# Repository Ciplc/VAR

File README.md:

# VAR
The VAR repository.
For those of you new to C++ here are two resources that I found helpful:
http://www.learncpp.com/
https://www.youtube.com/watch?v=mUQZ1qmKlLY

For those of you new to Python, talk to me for help in addition to
looking up several tutorials online, most tutorials are perfectly 
fine to learn from. Learning by doing is a great technique.

To commit to master you must verify your commits using GPG keys. Merging requires 1 reviewer.

## Acronyms

**ERPI** : Emulated Rasperry Pi

**RPI**  : Rasperry Pi

**RTC**  : Real time clock

**CMP**  : Civilian Missiles Program

**PS**   : Project Stratosphere

**-v**   : Version

**ASS**  : Acronyms Seriously Suck

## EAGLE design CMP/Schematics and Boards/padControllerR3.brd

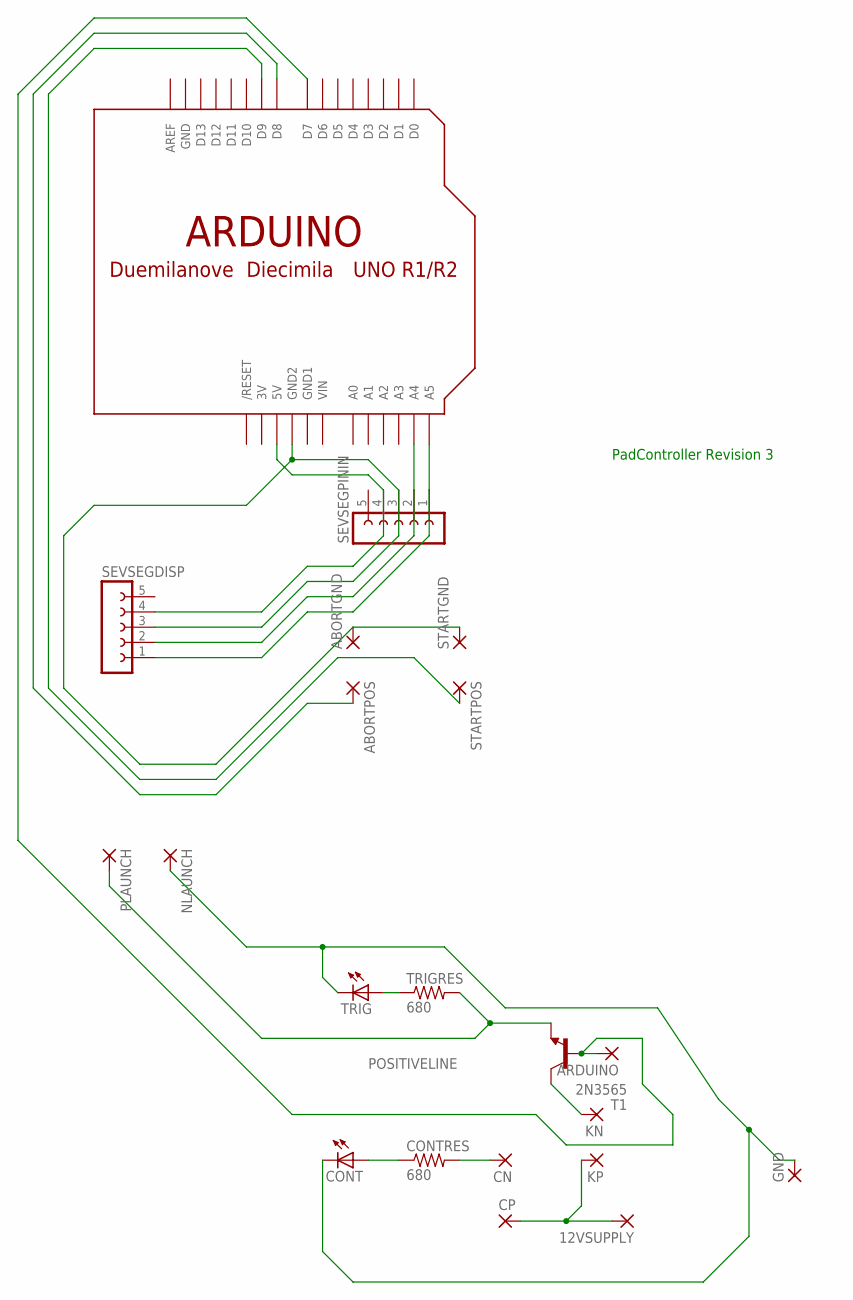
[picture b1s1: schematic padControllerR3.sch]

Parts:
12VSUPPLY: 3,17/1,1
ABORTGND: 3,17/1,3
ABORTPOS: 3,17/1,3
ARDUINO: 3,17/1,3
CN: 3,17/1,3
CONT: LED3MM
CONTRES: 680; 0207/7
CP: 3,17/1,3
GND: 3,17/1,1
KN: 3,17/1,3
KP: 3,17/1,3
NLAUNCH: 3,17/1,1
PLAUNCH: 3,17/1,1
SEVSEGDISP: FE05-1
SEVSEGPININ: FE05-1
STARTGND: 3,17/1,3
STARTPOS: 3,17/1,3
T1: 2N3565; TO92
TRIG: LED3MM
TRIGRES: 680; 0207/7
U$1: ARDUINO-NOHOLE

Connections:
3V: U$1.3V
GND: U$1.GND
GND1: U$1.GND1
unnamed: 12VSUPPLY.1, CP.1, KP.1
unnamed: KN.1, T1.1 (C)
unnamed: ABORTPOS.1, U$1.D8
unnamed: SEVSEGDISP.4, SEVSEGPININ.4, U$1.5V
unnamed: TRIG.A, TRIGRES.1
unnamed: CONT.K (C), GND.1, NLAUNCH.1, TRIG.K (C)
unnamed: CN.1, CONTRES.2
unnamed: CONT.A, CONTRES.1
unnamed: ARDUINO.1, T1.2 (B), U$1.D7
unnamed: STARTPOS.1, U$1.D9
unnamed: ABORTGND.1, SEVSEGDISP.3, SEVSEGPININ.3, STARTGND.1, U$1.GND2
unnamed: SEVSEGDISP.2, SEVSEGPININ.2, U$1.A4
unnamed: SEVSEGDISP.1, SEVSEGPININ.1, U$1.A5
POSITIVELINE: PLAUNCH.1, T1.3 (E), TRIGRES.2
VIN: U$1.VIN

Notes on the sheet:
PadController Revision 3

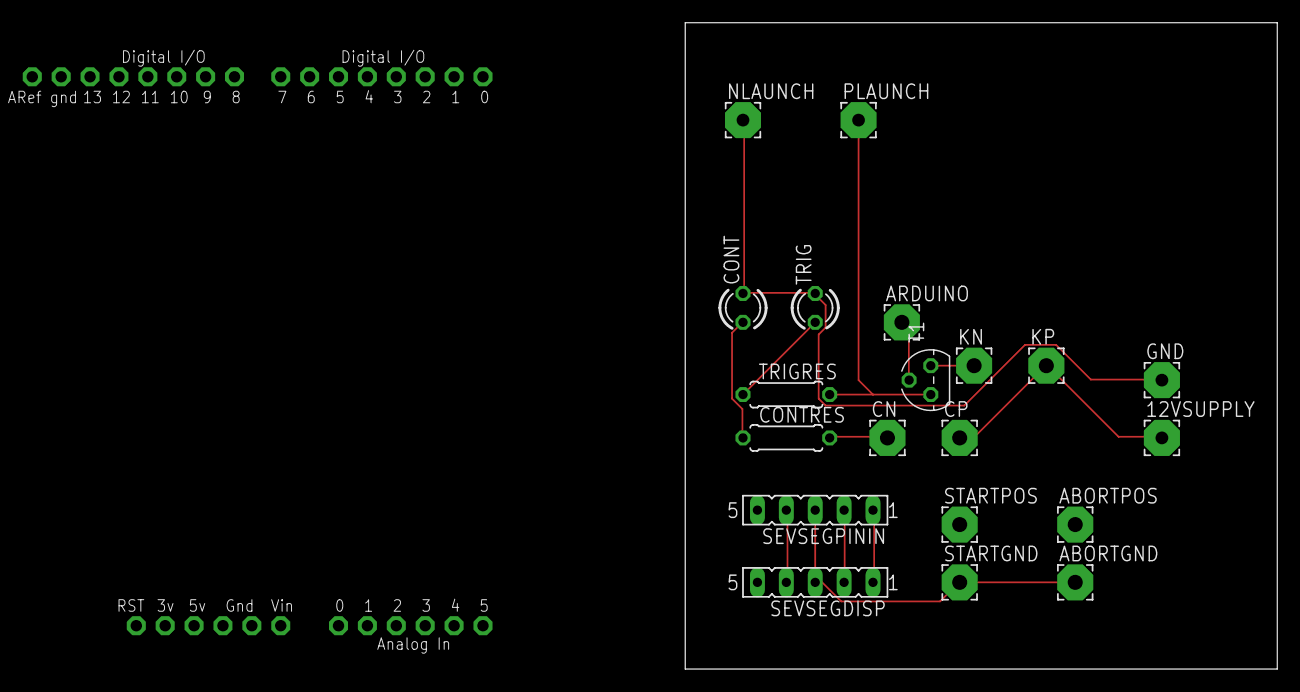
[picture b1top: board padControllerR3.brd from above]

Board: 2 copper layers, 52.0 x 56.8 mm, 21 parts (0 on the bottom side), 14 nets.

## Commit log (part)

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2018-03-09 Changed wording on the README
2018-03-09 Testing functionality
2018-03-09 Deleted Testdoc
2018-03-09 Idk what this is
2018-03-09 Revert "Idk what this is"
    This reverts commit 0c9a59654bc4afbc13fb859d9d42e313b337d4cf.
2018-03-09 Deleted testclass
2018-03-11 Added projectplanning file
    Added a file to be used for the tracking and planning of the progress of this project.
2018-03-11 Website
    Started work on a small website because we have nothing to work on in the mean time.
2018-03-11 Updated template CSS
2018-03-11 Added a contact us section
2018-03-12 Corrected index, updated misison statement
    Corrected a spelling error in index and updated the mission statment to the official one.
2018-03-12 Added an about us page
2018-03-12 Added html file structure
2018-03-22 Grammar change
2018-04-01 Created main.cpp
    Created main.cpp to hold the core of the pad control.
2018-04-03 Added PadReqs
2018-04-03 Removed main.cpp
    Removed main.cpp as it is useless for pad control as using a sketch made in the Arduino IDE is easier.
2018-04-03 Removed test code
    see title
2018-04-03 Basic abort
    Connect button to pin 2, press button toggle led and abort will be triggered.
2018-04-04 V0.2
    Fixed a typo that would have caused an error.
2018-04-04 Updated PagReqs to current
2018-04-05 V 0.2
    Updated Pseudo
2018-04-06 Removed extra copy of Pseudo
2018-04-06 V.21
    Created padControl, the final program for the Pad Controller.
2018-04-06 V .22
    Added abort IF statement, preliminary abort();. Not sure if we want to stop the countdown then throw error codes then end the program loop later.
2018-05-02 V.24
    Moved onto padControl Revision 2, padContorl Revision 1 has been removed permenantly.
2018-05-02 V.25
    Removed SevSeg Demo Library
2018-05-08 V 0.26
    Addded details to padReqs.
    Added a pinout for padCtrlr.
    Added a launch function to padCtrl.
2018-05-14 V .27
    V .27:
    Added Abort functionality
    Updated Pinout
2018-05-14 V .28
    Added StartButton support
    Updated PadReqs and Pinout
2018-05-15 V 0.281
    V 0.281
    Removed abortSequence.ino
2018-05-15 V 0.1
    V 0.1
    Removed all HTML content
2018-05-15 Deleted .DS_Store
2018-05-15 Create LICENSE
2018-05-15 Housekeeping
    Removed outdated file
2018-05-15 ignoreDS_Store
2018-08-14 V.29
    Updated functionality
2018-11-02 REPO restructure
    Reworked the repo structure to be for the VAR program so as to be able to consolidate to one repo for all VAR projects.
2018-11-09 Added documentation
2018-11-09 started R3 of the padControl
    renamed padcontrolR2 to padcontrol
    added padControlR3 which has better documentation for future reference.
2018-11-09 added documentation to abort sequence
2018-11-09 added no start approval error
2018-11-09 updating padreqs
2018-11-09 test please ignore
2018-11-09 Test 2 please ignore
2018-11-09 test4 the usual
2018-11-09 lowered time to enable faster testing by default
2018-11-12 Added a placeholder for the flightcomputer script
2018-11-12 Updated .gitignore
2018-11-12 Added placeholder text
2018-11-12 Added clarity to sense_emu
2018-11-12 ERPI tested and modified datawrite.py, example .csv included
2018-11-12 Fixed accelerometer output
2018-11-12 Updated .csv and time, non crashy programing
2018-11-13 Updated datawrite.py to fit the project reqs Build not confirmed with ERPI or RPI
2018-11-13 Added datetime to datawrite.py, created a csv pre-format tool Added requirements file for the RPI datawrite.py untested on ERPI and RPI
2018-11-13 Fixed datawrite.py, data.csv example included ERPI tested
2018-11-13 Documentation update
2018-11-13 Updated counter in datawrite.py
2018-11-13 Tested on ERPI, modifying on other machine
2018-11-13 Testing on ERPI
2018-11-13 Develop on other machine
2018-11-13 modified .gitignore
2018-11-14 Fixed whitespace errors on datawrite.py, added to .gitignore Not ERPI tested
2018-11-14 Formating changes, testing on ERPI build not tested on ERPI or RPI
2018-11-14 Updated datawrite.py to not crash when specifying CLI args Not tested on ERPI and RPI
2018-11-14 Tested on ERPI revising
2018-11-14 Removed debugging code and added documentation Throws exit(0) if more than 1 arg is provided
2018-11-14 Added readme for datawrite.py
2018-11-14 Removed placeholder
2018-11-15 Updated documentation on datawrite.py, csvsetup.py
2018-11-15 Basic framework for datalogging with the flight computer
2018-11-15 Adapted to work with CSV files
2018-11-15 Updated log from .txt to .csv
2018-11-15 Added space for declarations
2018-11-15 Updated method for saving
2018-11-15 Version of the flight computer which compiles but doesn't record or act on data
2018-11-15 Reorganized structure to account for flight computer
2018-11-15 Added readme's for each program andd a pinout for the flight computer
2018-11-16 Added init.py to increase future usability
2018-12-03 Updated documentation in datawrite.py
2018-12-06 Setup methods for basic thrust vectoring theory
2018-12-06 Updated output method, added servo library
2018-12-30 Updated .gitignores
2019-01-25 Added base for flightcompr2
2019-01-25 Added camera run tracker using json and updated git ignore
2019-01-25 Added camera starting to the init.
2019-01-25 Updated git ignore
2019-01-28 Added stopping mechanism for the camera
2019-01-28 Updated Documentation
2019-01-29 Added base for math for inverse point finding
2019-02-01 rewrote in class relationship with PEP8 standard
2019-02-02 Started docstrings
2019-02-02 Updated documentation on entire file
2019-02-03 Updated main method to remove default and catch argv errors
2019-02-03 Updated readme.md to reflect changes in prev. commit
2019-02-08 Restructured PS file structure and saved old scripts in psOld for use in case of an error with testing. Updated readme.mdd to reflect new script name.
2019-02-08 Updated error catching to be more specific and actually function as intended
2019-02-08 Added looping functionality as a temporary measure until the RTC can be implement to RPI
2019-02-19 Fixed issue with constructor which lead to self being unfilled in datawriting
2019-04-11 Initial groundwork for padctonrolr4, src is for src, build is .class, lib is for external jars
2019-04-11 Updated Placeholders for packages
2019-04-11 The serial scanning may now work, not sure haven't tested too much. Removed build folder and updated gitignore to stop it from being added in the future
2019-04-11 Updated documentation so that there was some to try and make sense of this mess.
2019-04-11 Tested port getting method, works flawlessly. Checked serial_open also works well. Removed pointless method
2019-04-11 added value in serial.java and updated readme.md
2019-04-11 Removed old serial class and added new updated serialconnection class in its place, functions nominally testing is needed
2019-04-11 Added framework for adapting to a user selected device.
2019-04-12 Updated methodology to be able to handle connection opening better
2019-04-15 Setup placeholder for arduino program w/ header
2019-04-16 Creates welcome frame.
2019-04-16 Removed placeholder and added src to correct location
2019-04-16 Expanded methods for readability
2019-04-16 Removed artifacts of old project
2019-04-16 Ignored build file
2019-04-16 Possible patch for project structure
2019-04-16 renamed package to gui
2019-04-16 Updated constructor
2019-04-16 Added base for Poll
2019-04-16 Added template to be used if wanted, delete it if you don't want to use it
2019-04-16 Added Poll.java with template example, optimized imports in Welcome.java
2019-04-16 Updated: Template.java Welcome.java / Added: VAR.png
2019-04-16 Updated: Template.java (Test method)
2019-04-16 Removed error causing import
2019-04-17 Fixed issue with setting a specific port on SerialPort obj
2019-04-17 Updated: Poll.java, Template.java, Welcome.java
2019-04-17 Updated: Poll.java
2019-04-17 Finished serial connection and serialData sending
2019-04-18 Added base for input frame
2019-04-18 Added template for data obj to work with GUI
2019-04-18 Added basic Objs for Input frame, fixed spacing on Poll frame
2019-04-18 Updated: notes.txt , Input.java Edited some of the notes to add goals. Commented out test method in Input.java.
2019-04-18 Added basic template for timer frame and updated notes accordingly
2019-04-18 Added base for timer frame
2019-04-18 Finished: Poll.java / Updated: notes.txt ActionPerformed completed for Poll.java. Added No Go frame section in notes.txt.
2019-04-18 Updated: notes.txt Changed wording of some sections.
2019-04-18 Fractured version of the timer frame, need to fix ThreadTimer and get the Frame to update
2019-04-18 Modifed declaration of counter to be more friendly to use
2019-04-19 WIP TimerFrame, needs to have ThreadTimer obj refresh constantly
2019-04-21 Minor changes that dont change much, just need to switch machines
2019-04-26 Removed duplicate import
2019-04-26 Updated: Poll.java Comments in ActionPerformed updated.
2019-04-27 test
2019-04-27 Trying wack stuff
2019-04-27 Wack stuff 2
2019-04-27 Slightly better working stuff
2019-04-27 Fixed typo that may have caused issues
2019-04-27 Fixed the video, working on error in outputting data to the csv
2019-04-27 Debugging time
2019-04-27 Changed datetime.now to datetime.now().strtime to make life maybe easier
2019-04-27 Changed to time only
2019-04-27 Messing with writer
2019-04-27 Patch to format
2019-04-27 Finished psbrain.py, everything ready for merge
2019-05-01 Moved button font to template so that it can be universal
2019-05-01 Finished LaunchNotification
2019-05-01 Updated Documentation, very minor
2019-05-01 mend
2019-05-01 base for nogoreminder
2019-05-01 Added import
2019-05-02 Added more panels and labels and started work on formatting them on to the frame
2019-05-02 Fixed spacing to improve clarity when reading
2019-05-02 Fixed some minor spacing
2019-05-02 Renamed data to Data to follow project convention
2019-05-02 Finished: noGoReminder.java / Updated: Template.java Note (noGoReminder.java): Added label warning user that all positions are ready and fixed formatting of frame. Note (Template.java): Added a warni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
2019-05-02 renamed noGoReminder
2019-05-02 Finished: noGoReminder.java (Added warning text notifying user that all positions are not go for launch. Fixed Close Operations to dispose rather than exit)
2019-05-02 Trying to fix local repo
2019-05-02 trying to fix files
2019-05-02 Updating: Input.java (Working on buttons and inputs), noGoReminder.java ( updating file)
2019-05-02 Changed file name to fight double copy wack stuff
2019-05-02 same again, just actually this time
2019-05-03 Changed red warning color as to not be as harsh on the eyes
2019-05-03 Updated poll color for no go
2019-05-11 Added base docs
2019-05-13 Moved text wrapping
2019-06-24 Moving to the use of quaterion coordinate systems, writing in python first to test before implementing in C++
2019-06-25 Added servo test program, should work, untested
2019-06-27 Removed old methods and added some documentation
2019-06-28 Work in progress version of the timer frame
2019-06-28 Minor Changes
2019-06-28 Worked on JFrame for Input.java / Updated notes.txt
2019-06-28 Added functionality to the program, just need to get the goal field working properly to proceed
2019-06-29 Fixed a minor visibility issue with the navigation buttons for Input.java
2019-06-29 Found something I can base my work on on Stack Overflow, testing from now
2019-06-29 Slimmed down working version, just need to have a way to vary the duration
2019-06-29 Documented the timer
2019-06-29 Welcome.java now opens Input.java when "Next" is pressed
2019-06-29 Started work on gui for TimerFrame.java
2019-06-29 Added TODO statements to pressure logging assignee to do their work
2019-06-29 Added more TODO remminders to pressure logging assigneeAdded more TODO remminders to pressure logging assigneeAdded more TODO remminders to pressure logging assigneeAdded more TODO remminders to pres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
2019-06-29 Finished gui for TimerFrame.java / Added new font to Template.java
2019-06-30 Working version of the checklist TODO add more items to track
2019-06-30 Made the the lifter name get mutliple words
2019-07-04 Created a startup script
    run it with nohup ./start.sh &
